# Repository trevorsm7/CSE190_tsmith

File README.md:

# CSE190_tsmith
Lab 1: I worked on Lab 1 with Daniel Knapp

Lab 3: I worked on Lab 3 with Ryan Collins

Lab 5: I worked on Lab 5 with David Smith

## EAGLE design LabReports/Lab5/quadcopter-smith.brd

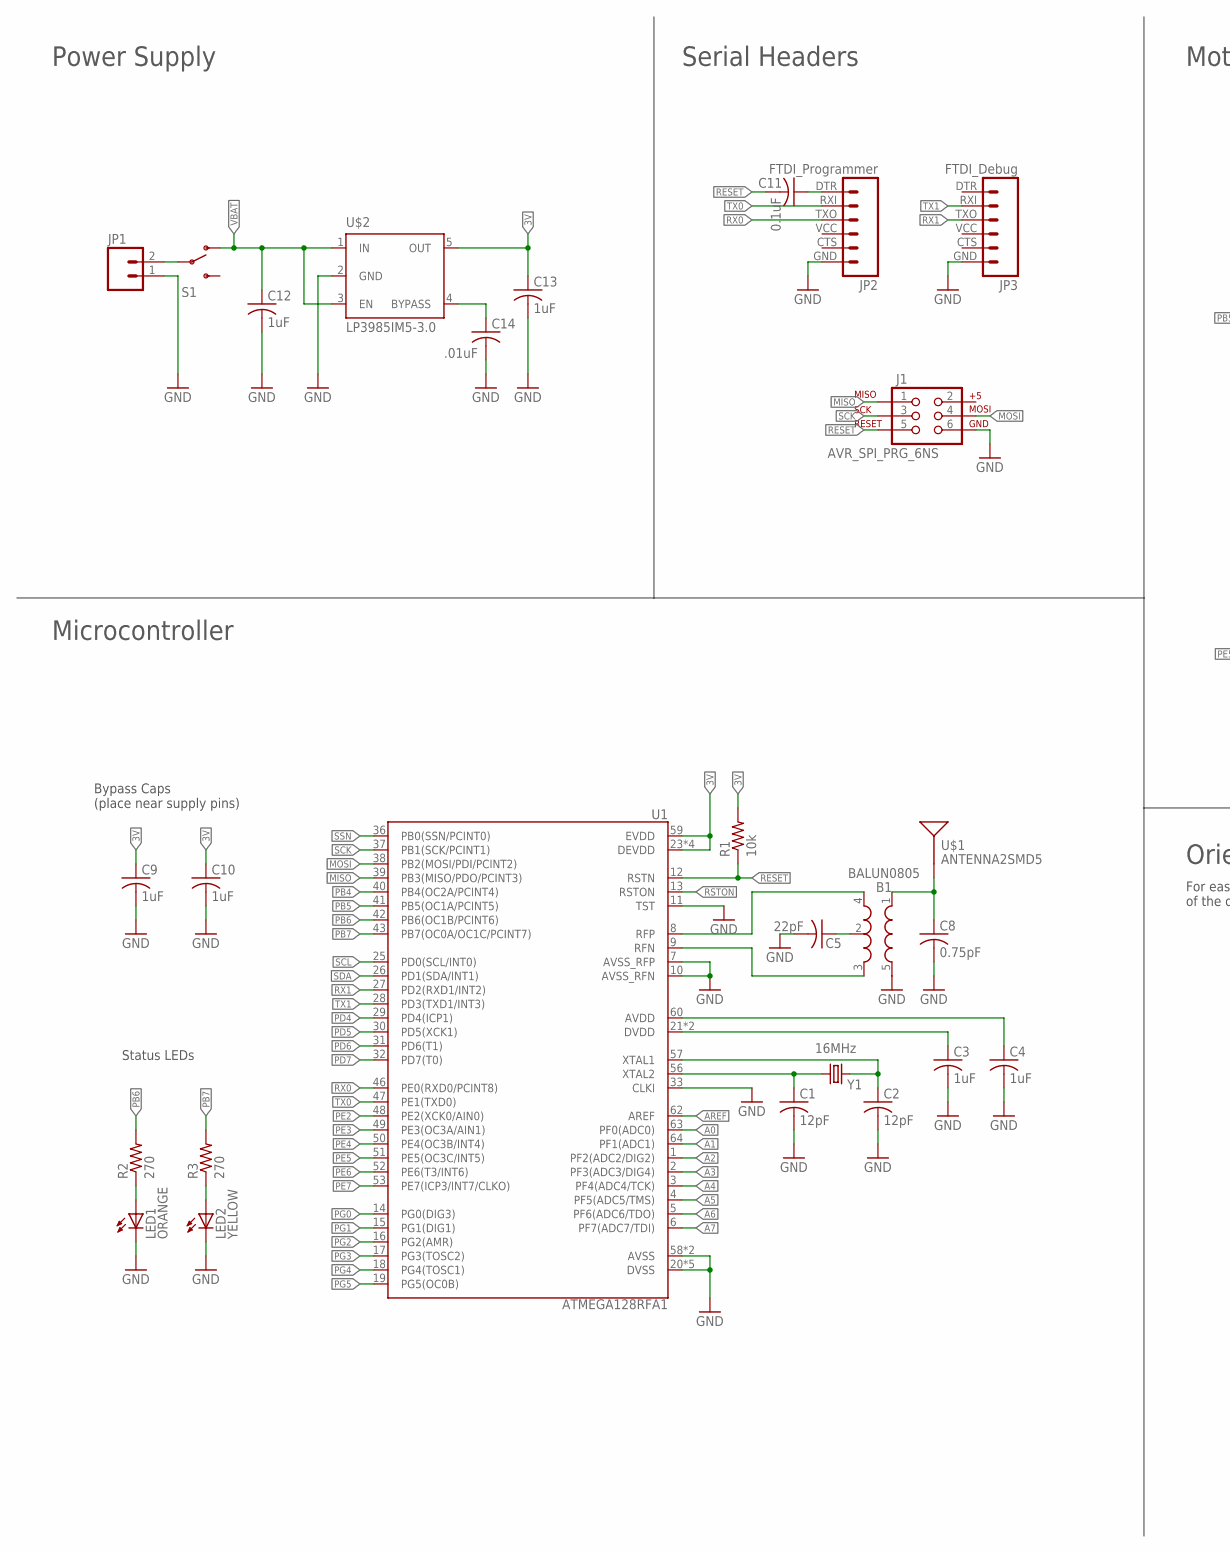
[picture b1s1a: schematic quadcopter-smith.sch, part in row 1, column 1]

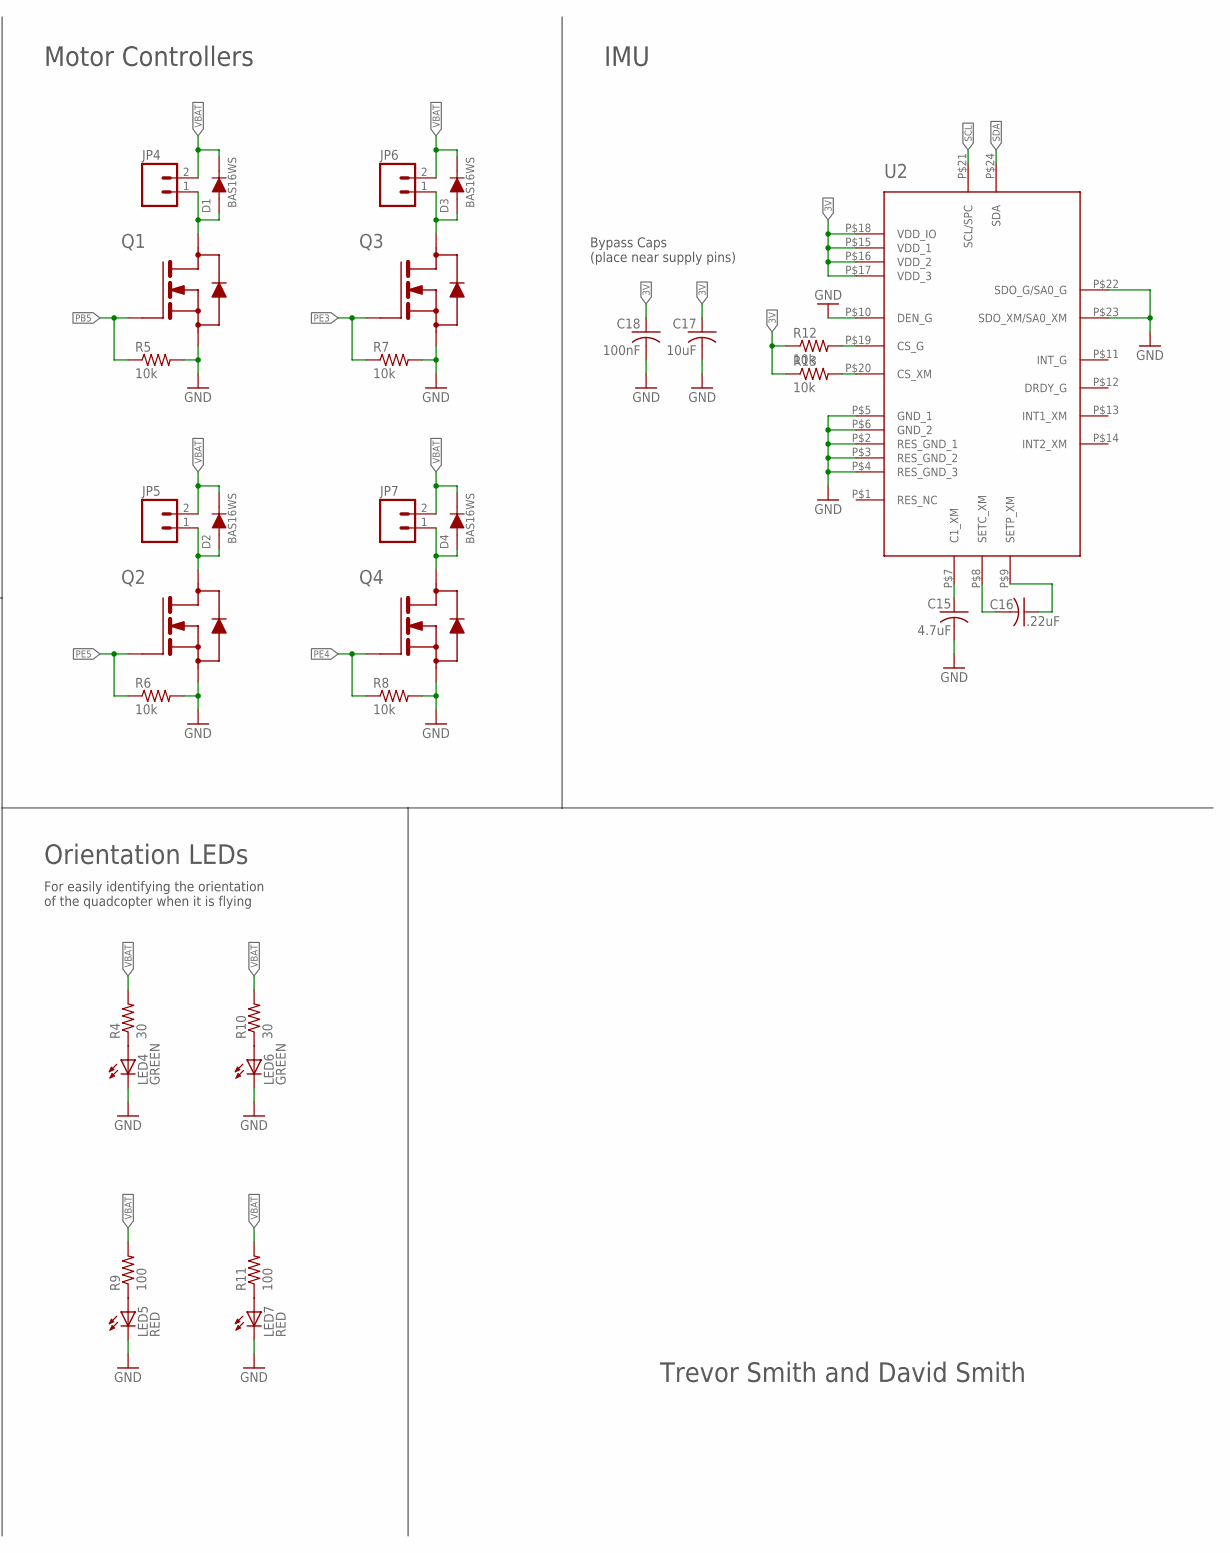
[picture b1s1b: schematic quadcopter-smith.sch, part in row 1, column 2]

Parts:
B1: BALUN0805; BALUN
C1, C2: 12pF; C0805
C3, C4, C9, C10, C12, C13: 1uF; C0805
C5: 22pF; C0805
C8: 0.75pF; C0805
C11: 0.1uF; C0805
C14: .01uF; C0805
C15: 4.7uF; C0805
C16: .22uF; C0805
C17: 10uF; C0805
C18: 100nF; C0805
D1, D2, D3, D4: BAS16WS; SOD-323
J1: AVR_SPI_PRG_6NS; 2X3-NS
JP1, JP4, JP5, JP6, JP7: M02PTH; 1X02
JP2: FTDI_Programmer; FTDI_BASIC
JP3: FTDI_Debug; FTDI_BASIC
LED1: ORANGE; CHIP-LED0805
LED2: YELLOW; CHIP-LED0805
LED4, LED6: GREEN; CHIP-LED0805
LED5, LED7: RED; CHIP-LED0805
Q1, Q2, Q3, Q4: SI2302CDS; SOT-23
R1, R5, R6, R7, R8, R12, R13: 10k; R0805
R2, R3: 270; R0805
R4, R10: 30; R0805
R9, R11: 100; R0805
S1: SWITCH-SPDTPTH; SWITCH-SPDT
U1: ATMEGA128RFA1; QFN-64
U2: LSM9DS0-LGA24; LGA-24
U$1: ANTENNA2SMD5; ANTENNA-CHIP5
U$2: LP3985IM5-3.0; SOT23-DBV
Y1: 16MHz; CRYSTAL-SMD-5X3

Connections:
3V: C9.1, C10.1, C13.1, C17.1, C18.1, R1.2, R12.1, R13.1, U1.23 (DEVDD), U1.34 (DEVDD), U1.44 (DEVDD), U1.54 (DEVDD), U1.59 (EVDD), U2.P$15 (VDD_1), U2.P$16 (VDD_2), U2.P$17 (VDD_3), U2.P$18 (VDD_IO), U$2.5 (OUT)
A0: U1.63 (PF0(ADC0))
A1: U1.64 (PF1(ADC1))
A2: U1.1 (PF2(ADC2/DIG2))
A3: U1.2 (PF3(ADC3/DIG4))
A4: U1.3 (PF4(ADC4/TCK))
A5: U1.4 (PF5(ADC5/TMS))
A6: U1.5 (PF6(ADC6/TDO))
A7: U1.6 (PF7(ADC7/TDI))
AREF: U1.62 (AREF)
GND: B1.5 (GND), C1.2, C2.2, C3.2, C4.2, C5.2, C8.2, C9.2, C10.2, C12.2, C13.2, C14.2, C15.2, C17.2, C18.2, J1.6, JP1.1, JP2.GND (6), JP3.GND (6), LED1.C, LED2.C, LED4.C, LED5.C, LED6.C, LED7.C, Q1.P$2 (S), Q2.P$2 (S), Q3.P$2 (S), Q4.P$2 (S), R5.2, R6.2, R7.2, R8.2, U1.7 (AVSS_RFP), U1.10 (AVSS_RFN), U1.11 (TST), U1.20 (DVSS), U1.24 (DVSS), U1.33 (CLKI), U1.35 (DVSS), U1.45 (DVSS), U1.55 (DVSS), U1.58 (AVSS), U1.61 (AVSS), U2.P$2 (RES_GND_1), U2.P$3 (RES_GND_2), U2.P$4 (RES_GND_3), U2.P$5 (GND_1), U2.P$6 (GND_2), U2.P$10 (DEN_G), U2.P$22 (SDO_G/SA0_G), U2.P$23 (SDO_XM/SA0_XM), U$2.2 (GND)
MISO: J1.1, U1.39 (PB3(MISO/PDO/PCINT3))
MOSI: J1.4, U1.38 (PB2(MOSI/PDI/PCINT2))
unnamed: C1.1, U1.56 (XTAL2), Y1.1
unnamed: C2.1, U1.57 (XTAL1), Y1.3 (2)
unnamed: C3.1, U1.21 (DVDD), U1.22 (DVDD)
unnamed: C4.1, U1.60 (AVDD)
unnamed: B1.3 (OUT2), U1.9 (RFN)
unnamed: B1.4 (OUT1), U1.8 (RFP)
unnamed: B1.1 (IN), C8.1, U$1.FEED
unnamed: B1.2 (GND), C5.1
unnamed: D2.P$1, JP5.1, Q2.P$3 (D)
unnamed: LED1.A, R2.1
unnamed: LED2.A, R3.1
unnamed: LED4.A, R4.1
unnamed: C11.1, JP2.DTR (1)
unnamed: C14.1, U$2.4 (BYPASS)
unnamed: JP1.2, S1.2
unnamed: D1.P$1, JP4.1, Q1.P$3 (D)
unnamed: D3.P$1, JP6.1, Q3.P$3 (D)
unnamed: D4.P$1, JP7.1, Q4.P$3 (D)
unnamed: C16.1, U2.P$9 (SETP_XM)
unnamed: C16.2, U2.P$8 (SETC_XM)
unnamed: C15.1, U2.P$7 (C1_XM)
unnamed: LED6.A, R10.1
unnamed: LED5.A, R9.1
unnamed: LED7.A, R11.1
unnamed: R12.2, U2.P$19 (CS_G)
unnamed: R13.2, U2.P$20 (CS_XM)
PB4: U1.40 (PB4(OC2A/PCINT4))
PB5: Q1.P$1 (G), R5.1, U1.41 (PB5(OC1A/PCINT5))
PB6: R2.2, U1.42 (PB6(OC1B/PCINT6))
PB7: R3.2, U1.43 (PB7(OC0A/OC1C/PCINT7))
PD4: U1.29 (PD4(ICP1))
PD5: U1.30 (PD5(XCK1))
PD6: U1.31 (PD6(T1))
PD7: U1.32 (PD7(T0))
PE2: U1.48 (PE2(XCK0/AIN0))
PE3: Q3.P$1 (G), R7.1, U1.49 (PE3(OC3A/AIN1))
PE4: Q4.P$1 (G), R8.1, U1.50 (PE4(OC3B/INT4))
PE5: Q2.P$1 (G), R6.1, U1.51 (PE5(OC3C/INT5))
PE6: U1.52 (PE6(T3/INT6))
PE7: U1.53 (PE7(ICP3/INT7/CLKO))
PG0: U1.14 (PG0(DIG3))
PG1: U1.15 (PG1(DIG1))
PG2: U1.16 (PG2(AMR))
PG3: U1.17 (PG3(TOSC2))
PG4: U1.18 (PG4(TOSC1))
PG5: U1.19 (PG5(OC0B))
RESET: C11.2, J1.5, R1.1, U1.12 (RSTN)
RSTON: U1.13 (RSTON)
RX0: JP2.TXO (3), U1.46 (PE0(RXD0/PCINT8))
RX1: JP3.TXO (3), U1.27 (PD2(RXD1/INT2))
SCK: J1.3, U1.37 (PB1(SCK/PCINT1))
SCL: U1.25 (PD0(SCL/INT0)), U2.P$21 (SCL/SPC)
SDA: U1.26 (PD1(SDA/INT1)), U2.P$24 (SDA)
SSN: U1.36 (PB0(SSN/PCINT0))
TX0: JP2.RXI (2), U1.47 (PE1(TXD0))
TX1: JP3.RXI (2), U1.28 (PD3(TXD1/INT3))
VBAT: C12.1, D1.P$2, D2.P$2, D3.P$2, D4.P$2, JP4.2, JP5.2, JP6.2, JP7.2, R4.2, R9.2, R10.2, R11.2, S1.1 (O), U$2.1 (IN), U$2.3 (EN)

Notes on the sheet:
Power Supply
Serial Headers
Motor Controllers
Microcontroller
IMU
Bypass Caps (place near supply pins)
Status LEDs
Orientation LEDs
Trevor Smith and David Smith
For easily identifying the orientation of the quadcopter when it is flying

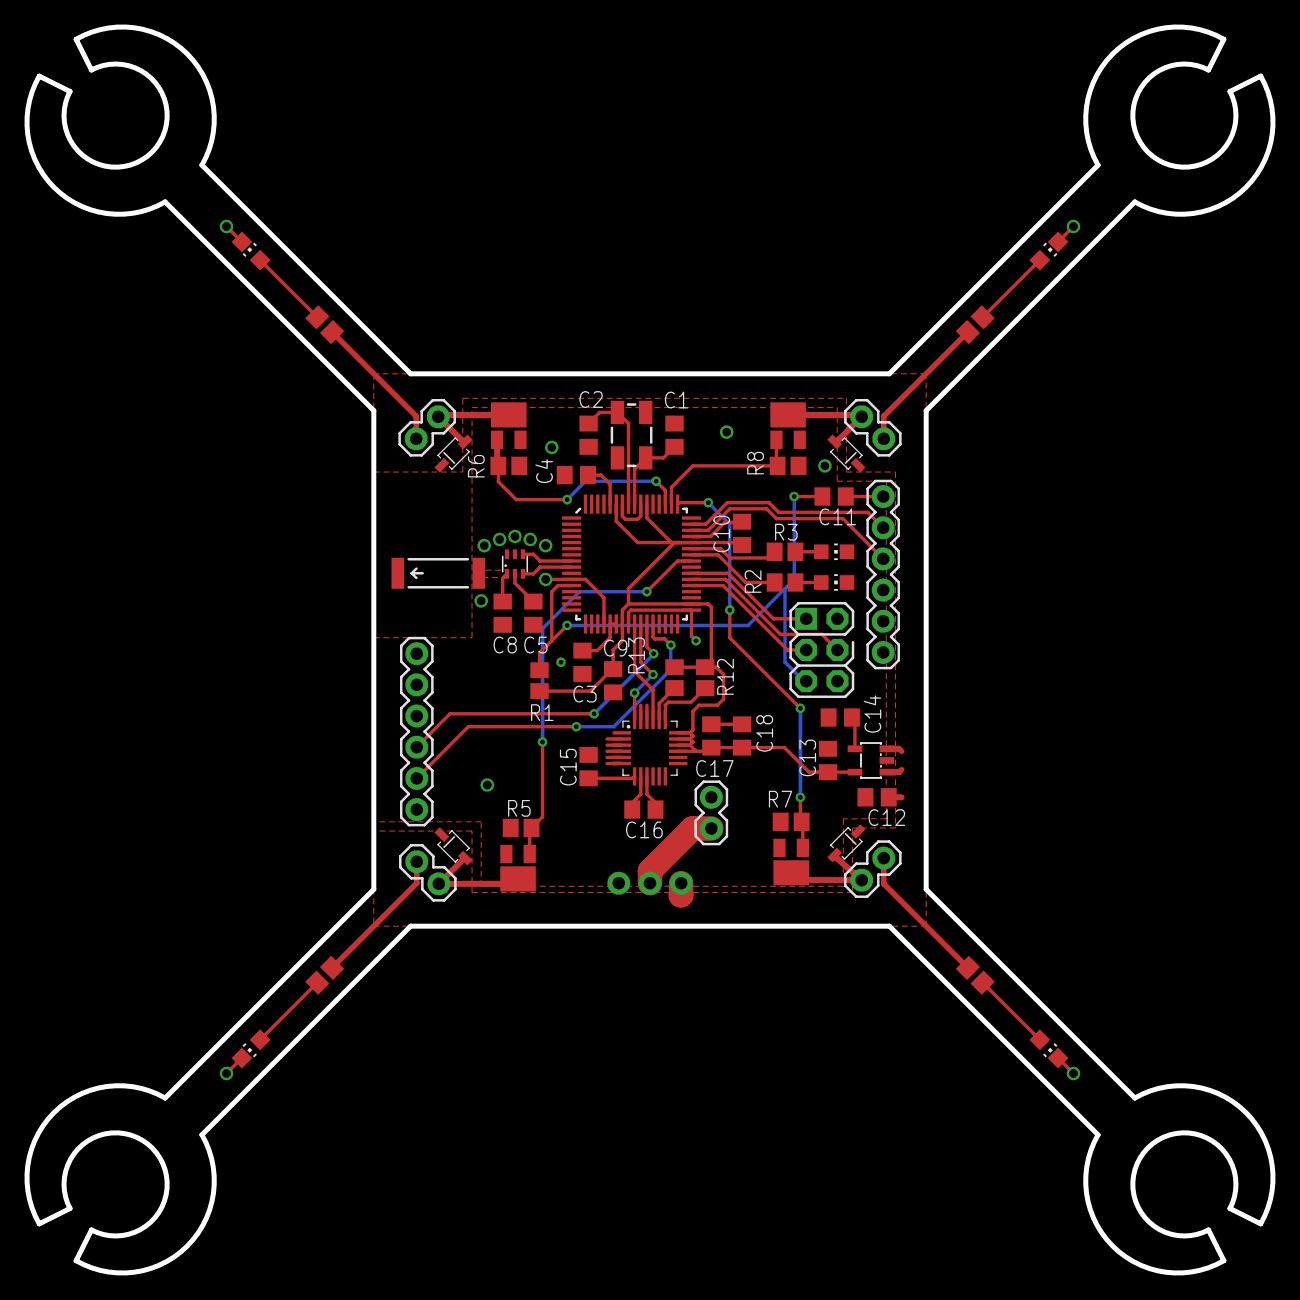
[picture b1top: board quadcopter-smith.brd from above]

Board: 2 copper layers, 101.5 x 101.5 mm, 59 parts (1 on the bottom side), 45 nets.

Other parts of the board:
U$3: LOGO

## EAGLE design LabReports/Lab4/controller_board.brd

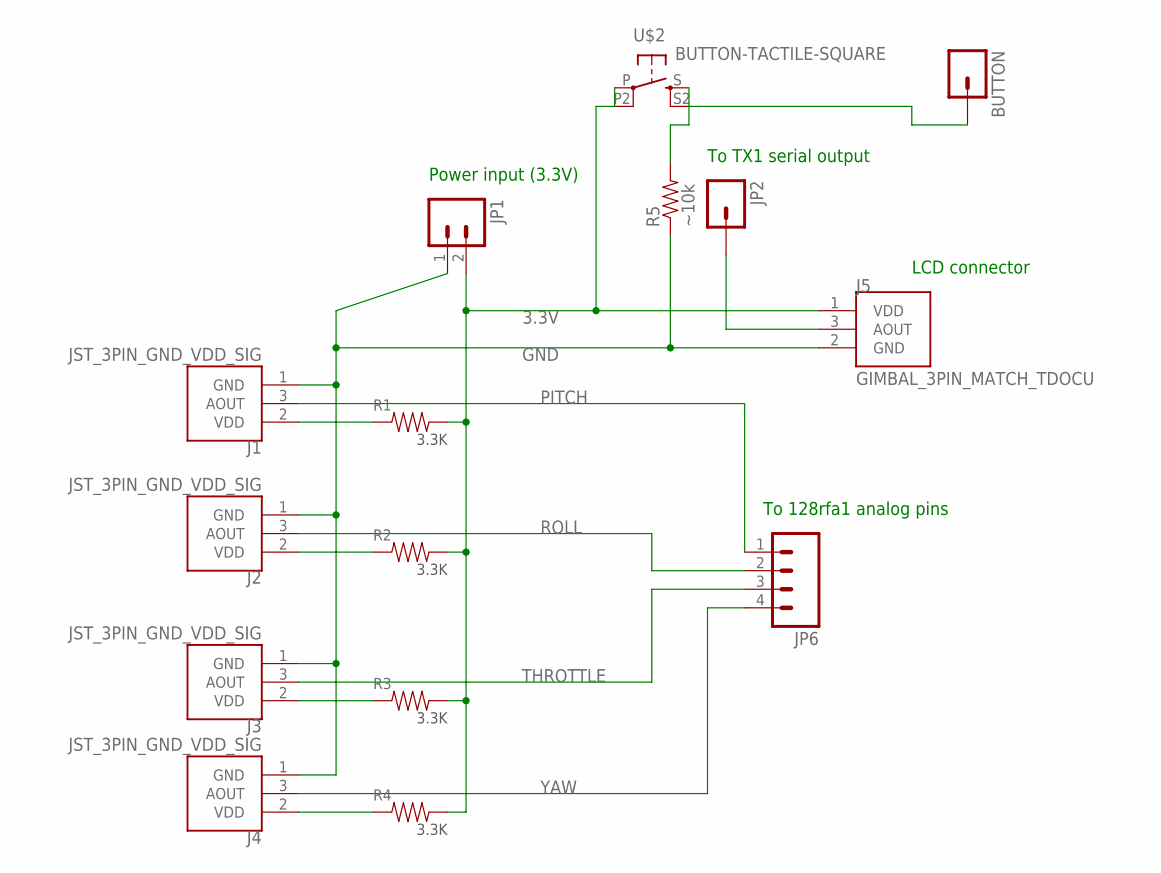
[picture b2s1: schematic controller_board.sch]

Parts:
BUTTON: M01PTH; 1X01
J1, J2, J3, J4: JST_3PIN_GND_VDD_SIG; JST-3-PTH-REVERSE
J5: GIMBAL_3PIN_MATCH_TDOCU; JST-3-PTH
JP1: M021X02_NO_SILK; 1X02_NO_SILK
JP2: M01PTH; 1X01
JP6: M04PTH; 1X04
R1, R2, R3, R4: 3.3K; CFR-12
R5: ~10k; AXIAL-0.4
U$2: BUTTON-TACTILE-SQUARE; BUTTON-TACTILE-SQUARE-ADAFRUIT1010

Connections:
3.3V: J5.1 (VDD), JP1.2, R1.P$2, R2.P$2, R3.P$2, R4.P$2, U$2.P, U$2.P2 (P1)
GND: J1.1 (GND), J2.1 (GND), J3.1 (GND), J4.1 (GND), J5.2 (GND), JP1.1, R5.P$1 (1)
unnamed: J1.2 (VDD), R1.P$1
unnamed: J2.2 (VDD), R2.P$1
unnamed: J3.2 (VDD), R3.P$1
unnamed: J4.2 (VDD), R4.P$1
unnamed: BUTTON.1, R5.P$2 (2), U$2.S, U$2.S2 (S1)
unnamed: J5.3 (AOUT), JP2.1
PITCH: J1.3 (AOUT), JP6.1
ROLL: J2.3 (AOUT), JP6.2
THROTTLE: J3.3 (AOUT), JP6.3
YAW: J4.3 (AOUT), JP6.4

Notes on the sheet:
To 128rfa1 analog pins
LCD connector
Power input (3.3V)
To TX1 serial output

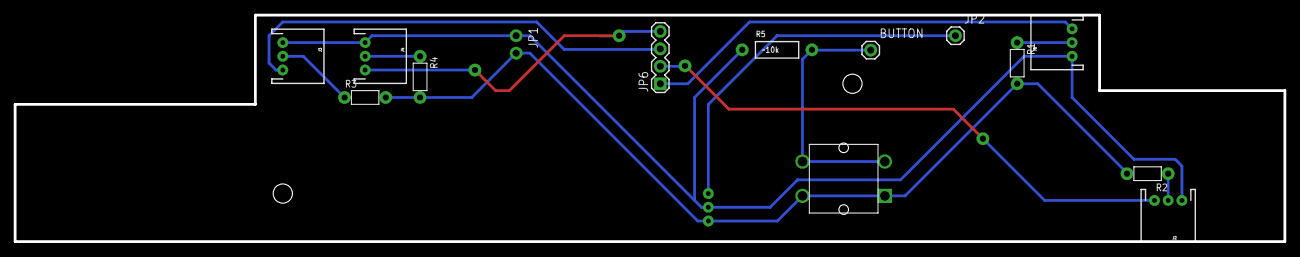
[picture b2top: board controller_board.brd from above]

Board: 2 copper layers, 185.0 x 33.0 mm, 16 parts (1 on the bottom side), 12 nets.

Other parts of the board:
U$1: CONNECTOR_BOARD_OUTLINE

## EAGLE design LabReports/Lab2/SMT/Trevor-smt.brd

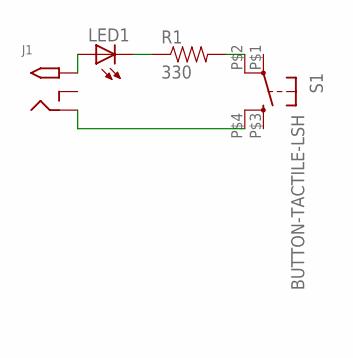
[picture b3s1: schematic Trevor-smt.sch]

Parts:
J1: 2.1MMJACKTHM; PJ-102A
LED1: LED3MM
R1: 330; AXIAL-0.3
S1: BUTTON-TACTILE-LSH; 1301.9315

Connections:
unnamed: J1.TIP, LED1.A
unnamed: LED1.K (C), R1.P$1 (1)
unnamed: R1.P$2 (2), S1.P$2 (P1)
unnamed: J1.RING, S1.P$4 (S1)

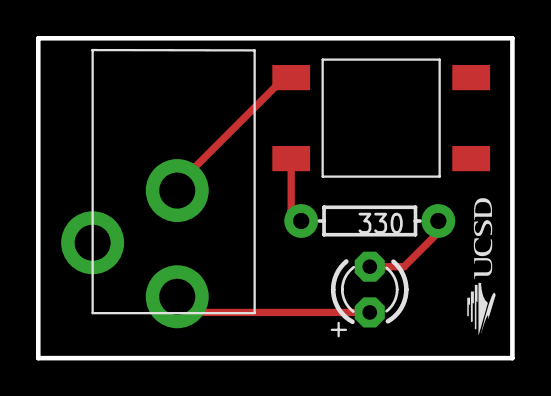
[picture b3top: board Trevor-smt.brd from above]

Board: 2 copper layers, 26.3 x 17.8 mm, 5 parts (0 on the bottom side), 4 nets.

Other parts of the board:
U$1: UCSD_LOGO

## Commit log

2015-04-03 Added sender code
2015-04-03 Added receiver code and writeup
2015-04-07 Lab2 through-hole
2015-04-07 Everything got fucked when I made a copy of the through hole board and schematic, so I moved the SMT stuff into a separate project
2015-04-07 Added SMT schematic and board
2015-04-10 Added lab 3 files
2015-04-13 Added parts to library
2015-04-13 Added resistors to schematic, but can't route with free version
2015-04-13 Added smt resistor
2015-04-16 Routed board and processed CAM
2015-04-22 Added lab 5 schematic
2015-04-23 Added grouping names and separators to schematic
2015-04-23 Beautified schematic
2015-04-28 Added design review of Dejun and Ryan
2015-04-29 modified schem after design review
2015-04-29 removed jumpers on balun circuit, connected tst and clki on atmega to gnd
2015-04-30 square board initial layout
2015-05-01 board outline mockup, time to try routing!
2015-05-01 end of Thursday lab hours
2015-05-01 shrink, route, modified some parts in Lab5.lbr
2015-05-01 Binged on manual routing
2015-05-01 Tweaked gnd via placement
2015-05-01 Adjusted some ground paths
2015-05-06 prepared board for peer review, exported CAM files
2015-05-07 add motor holders to frame
2015-05-07 for reals this time
2015-05-07 added Lab6 review of Dejun and Ryan
2015-05-07 added logo and restrict under IMU
2015-05-08 added readme to lab6 folder
2015-05-12 used new cam job
2015-05-15 Added BOM to Lab5 folder

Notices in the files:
parts and their libraries:
SparkFun-Connectors: Licensing: Creative Commons ShareAlike 4.0 International - https://creativecommons.org/licenses/by-sa/4.0
